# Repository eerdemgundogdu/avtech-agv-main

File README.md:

# AVTECH AGV: Forklift Robot

Software and carrier PCB design for a line-following forklift AGV built by CU AVTECH for the Sanayide Robotik Uygulamalar 2026 competition. The vehicle uses a hoverboard BLDC drivetrain, a Teensy 4.1 for real-time control and a Jetson Orin Nano as its high-level computer.

## Teensy firmware (`teensy_firmware/`)

- Non-blocking, time-sliced main loop: IMU at 100 Hz, motor commands at 20 Hz, telemetry at 10 Hz. No `delay()` calls on the control path.
- Hoverboard driver: speaks the EFeru FOC firmware's USART protocol (speed + steer frames, `0xABCD` start, XOR checksum) and parses feedback frames. Framing, checksum and speed ramping live in `hover_protocol.cpp`, unit-tested on the host.
- IMU: ICM-20948 over SPI with gyro bias calibration and a complementary filter for attitude/yaw.
- Heading hold: PI controller with gyro-rate damping locks the yaw at 50 Hz while driving straight.
- Forklift: DM556 stepper pulsed from an `IntervalTimer` ISR with position tracking, soft limits, homing and a hold-to-move keepalive.
- Navigation FSM: IDLE, MANUAL, LINE_FOLLOW, TURN, PICKUP/DROP, OBSTACLE_STOP and FAULT, plus a line-following PID (QTR-8A or camera offset from Jetson).
- Safety: manual-command timeout with ramp-down, Jetson link watchdog driven by heartbeats, motor outputs zeroed when inactive, and hardware/software E-stop path.
- Command parser: allocation-free JSON line parser with bounded buffers (`cmd_parser.cpp`, host-tested).

All pins, gains and timings are in `config.h`.

## Jetson software (`jetson_software/`)

- `avtech_brain.py`: Flask + Socket.IO control server sending drive input to the Teensy at a fixed 20 Hz with deadman timeout.
- `teensy_link.py`: serial link with PJRC VID auto-detection, port lock, auto-reconnect and 5 Hz heartbeat.
- `camera_node.py`: HSV color-line detection with perspective (bird's-eye) transform and ArUco markers.
- `qr_reader.py`: pick/drop task QR code reader.
- `ekf_localization.py`: Extended Kalman Filter over `[x, y, theta, gyro_bias]` fusing wheel odometry, gyro and QR landmark range/bearing measurements with Mahalanobis outlier gating (`ekf_test.py`).
- `sensor_fusion.py`: wraps the EKF and adds line/obstacle state.
- `mapping_node.py`: 2D occupancy grid built from odometry and ultrasonic sensors.
- `mission_control.py`: task sequencing.

## Carrier board (`hardware/`)

A 2-layer KiCad carrier board for the Teensy 4.1 (Rev A, 105x80 mm). It replaces hand wiring with a 24 V input stage (fuse, reverse-polarity diode, SMBJ30CA TVS), LMR16006X 24 V to 5 V buck, AP2112K-3.3 sensor LDO, BSS138 level shifters, HC-SR04 echo dividers, DM556 open-drain drivers, and a hardware E-stop contactor loop.

The schematic and PCB are generated from `hardware/gen/design.py` and checked with KiCad DRC/ERC. Fabrication outputs (Gerber, drill, BOM, pick-and-place, schematic PDF) are in `hardware/output/`. Design calculations: `hardware/DESIGN.md`; connector pinouts: `hardware/WIRING.md`.

## Testing and Build

```bash
cmake -S firmware_tests -B build/test && cmake --build build/test && ctest --test-dir build/test
cd jetson_software && python3 ekf_test.py
pio run -e teensy41_carrier
```

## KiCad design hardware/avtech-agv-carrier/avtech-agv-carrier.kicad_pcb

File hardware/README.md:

# AVTECH AGV Carrier Board (Rev A)

2-layer (105x80 mm, FR-4, 1.6 mm, 1 oz Cu) carrier board for the Teensy 4.1 forklift AGV.

Subsystems on the board:

- Power input: 1 A fuse, SS16 reverse-polarity diode, SMBJ30CA TVS, 47 uF bulk capacitor.
- 24 V to 5 V buck: LMR16006X (60 V, 0.6 A, 700 kHz), 22 uH inductor.
- 5 V to 3.3 V LDO: AP2112K-3.3 for sensors; Teensy VIN isolated through a B5819W Schottky diode.
- Hardware E-stop: NC button in series with the motor-power contactor coil, plus `MOTOR_EN` low-side switch (`BCP56-16`) and loop sense divider.
- Hoverboard UART: 3-pin connector (15 V pin omitted), 1k series resistors and BAT54S Schottky clamps.
- HC-SR04 x3: 5 V to 3.0 V echo voltage dividers.
- QTR-8A: powered from 3.3 V to keep analog outputs within the Teensy 4.1 ADC range.
- DM556 stepper: common-anode 5 V drive through AO3400A low-side MOSFETs.
- IMU: ICM-20948 over SPI0 with 33 ohm series damping resistors.

## Files

- `DESIGN.md`: design decisions, component calculations, PCB rules and bring-up checklist.
- `WIRING.md`: connector and Teensy 4.1 pin mapping.
- `avtech-agv-carrier/`: KiCad project, schematic and PCB files.
- `output/`: Gerber + drill zip, pick-and-place CSV, BOM, schematic PDF and DRC report.
- `gen/`: generator scripts (`python3 build.py`).

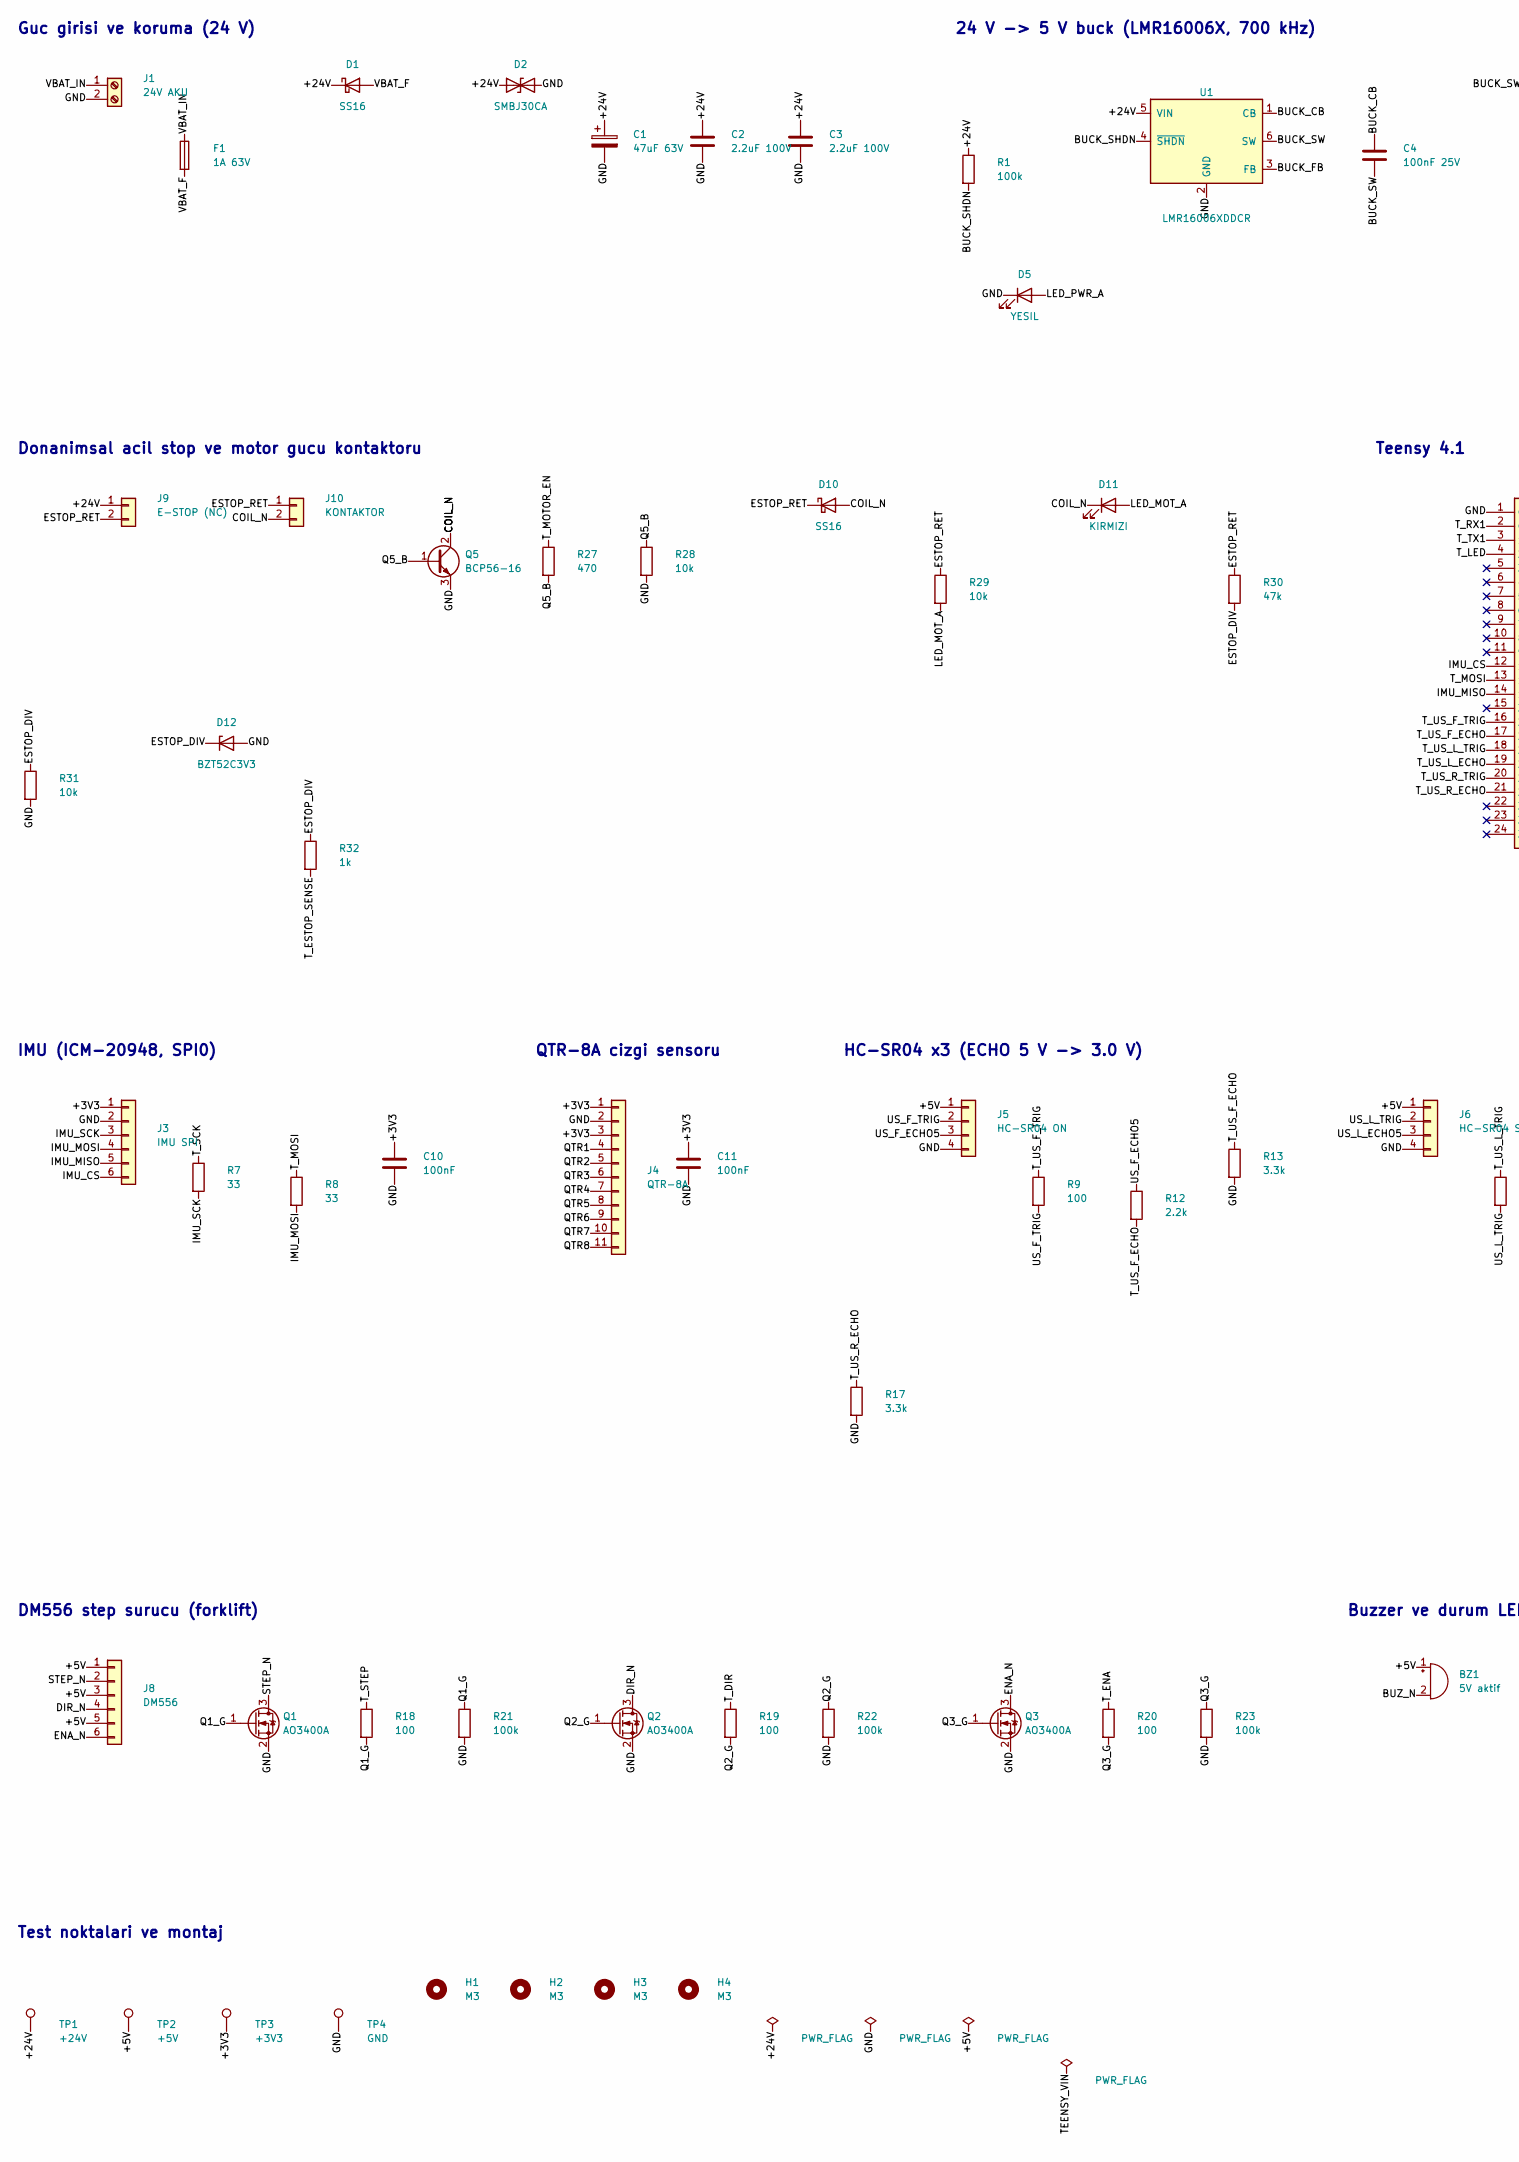
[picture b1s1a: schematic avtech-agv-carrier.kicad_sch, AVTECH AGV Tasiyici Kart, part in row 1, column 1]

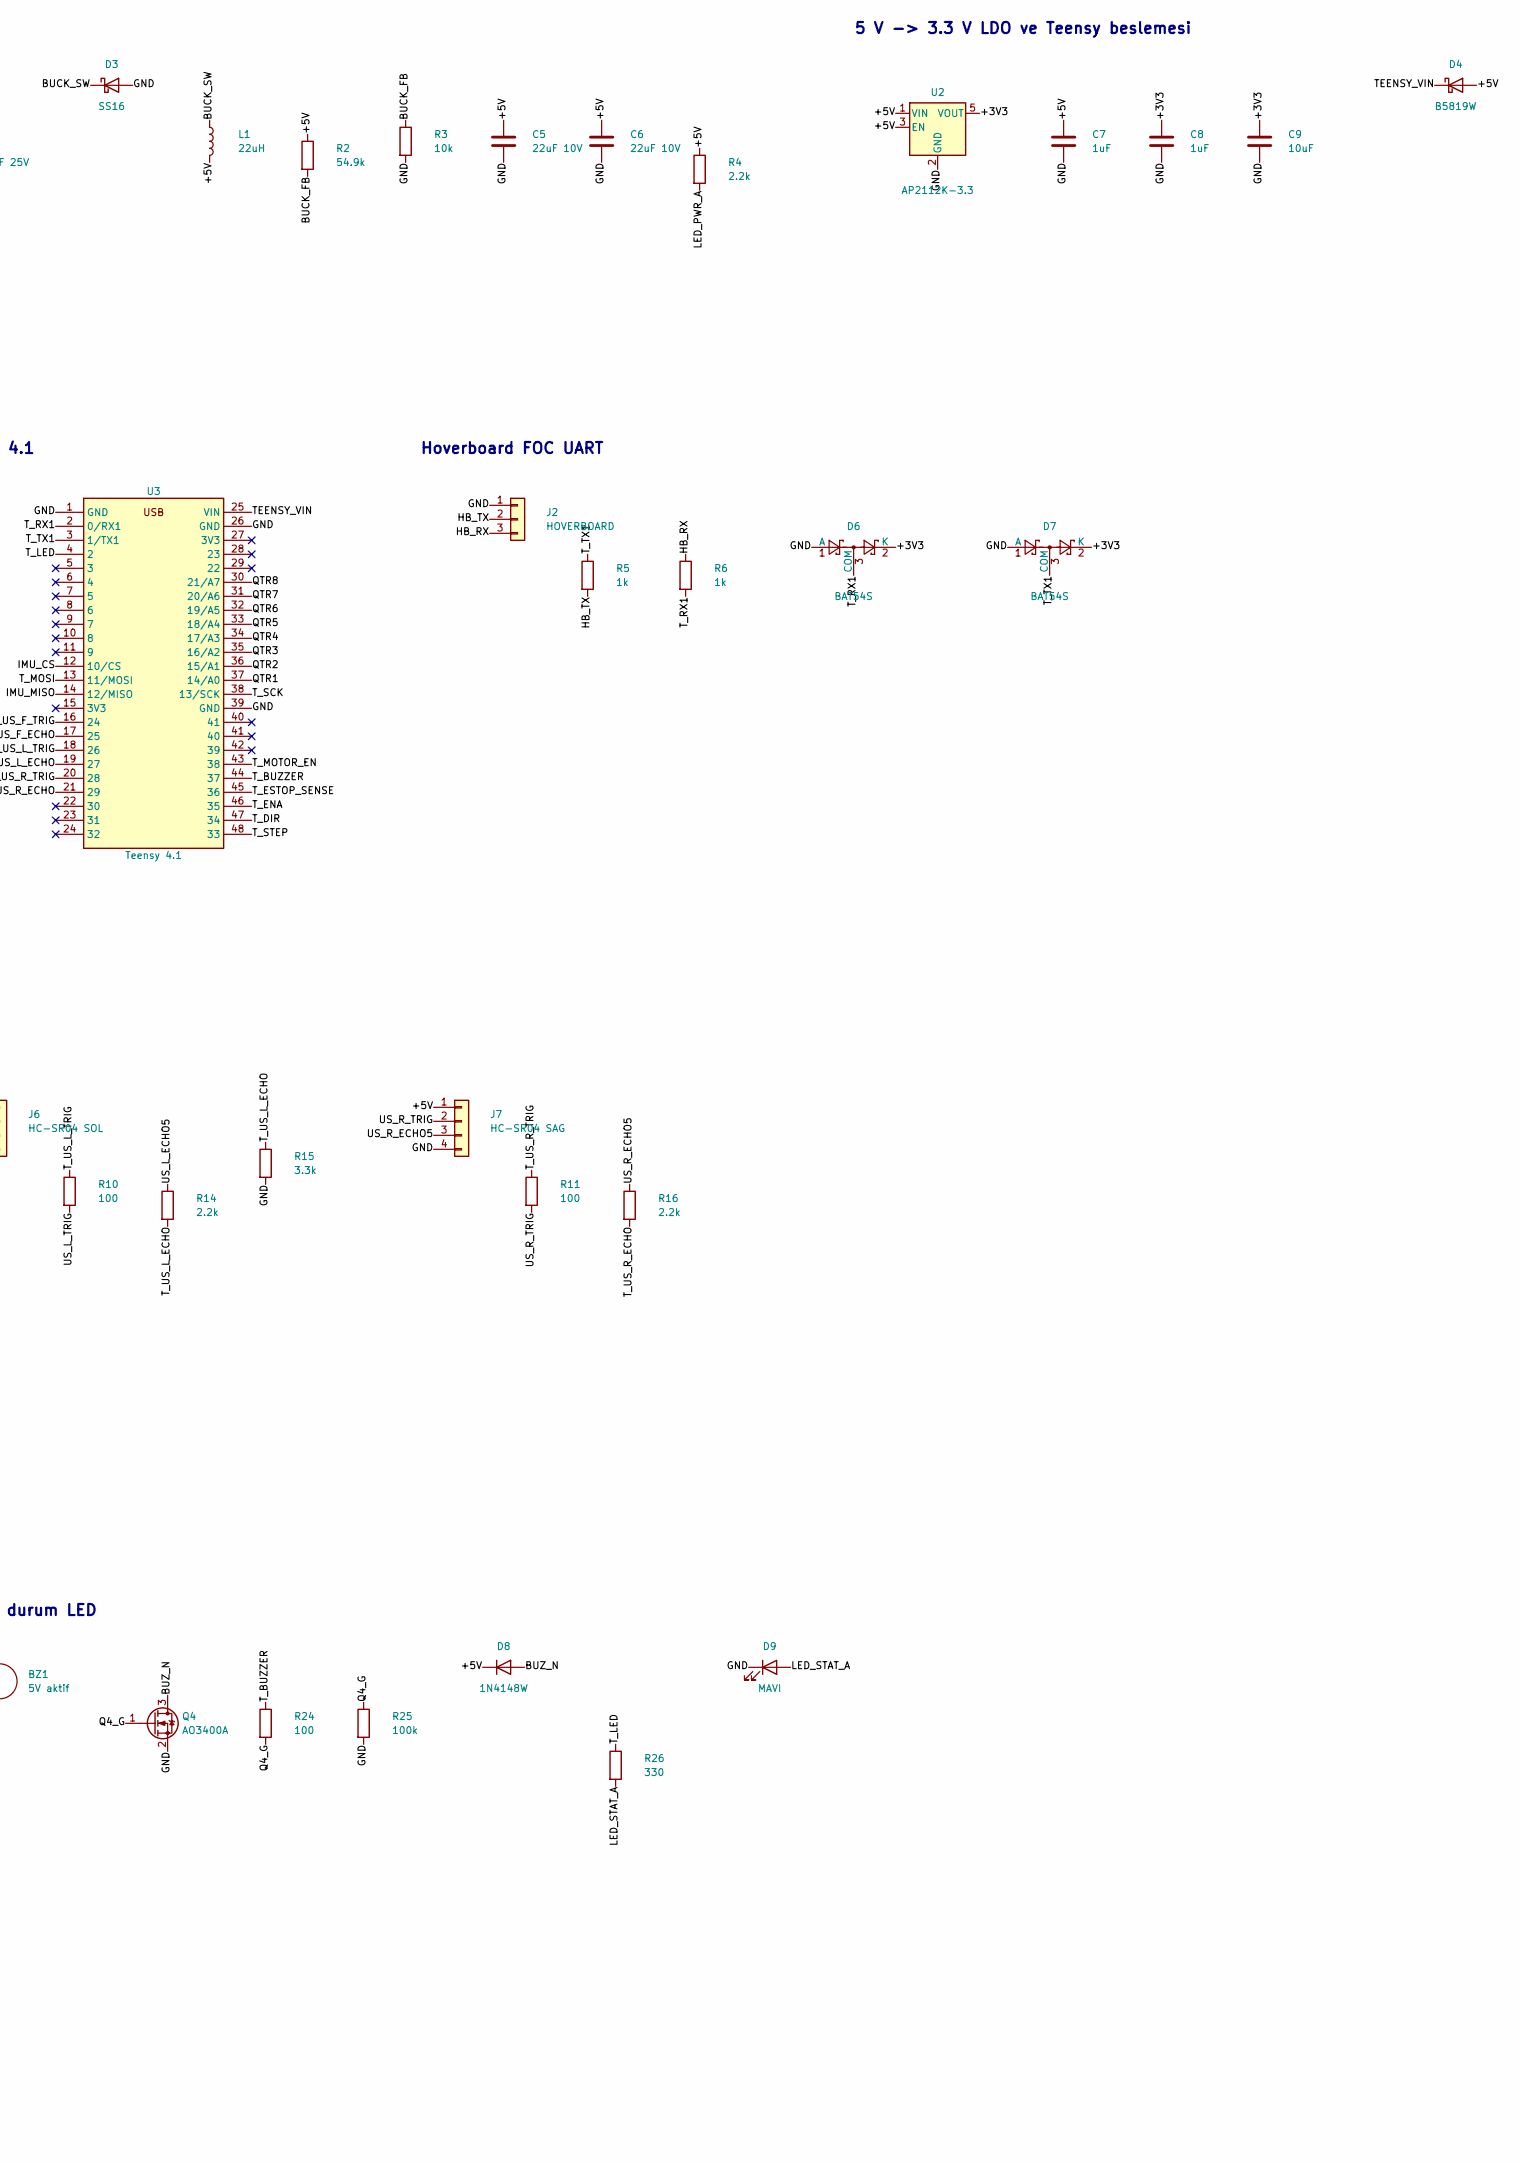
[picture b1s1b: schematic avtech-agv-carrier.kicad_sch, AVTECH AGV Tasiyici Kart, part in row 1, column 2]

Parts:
BZ1: 5V aktif; Buzzer_12x9.5RM7.6; MPN 12 mm 5V aktif buzzer
C1: 47uF 63V; CP_Elec_8x10; MPN Panasonic EEE-FK1J470P
C2, C3: 2.2uF 100V; C_1210_3225Metric; MPN X7R 1210 100V
C4: 100nF 25V; C_0603_1608Metric; MPN X7R 0603 25V
C5, C6: 22uF 10V; C_1206_3216Metric; MPN X7R 1206 10V
C7, C8: 1uF; C_0603_1608Metric; MPN X7R 0603 16V
C9: 10uF; C_0805_2012Metric; MPN X5R 0805 10V
C10, C11: 100nF; C_0603_1608Metric; MPN X7R 0603 16V
D1, D3, D10: SS16; D_SMA; MPN SS16 (60V 1A)
D2: SMBJ30CA; D_SMB; MPN Littelfuse SMBJ30CA
D4: B5819W; D_SOD-123; MPN B5819W (40V 1A)
D5: YESIL; LED_0603_1608Metric; MPN 0603 yesil LED
D6, D7: BAT54S; SOT-23; MPN BAT54S
D8: 1N4148W; D_SOD-323; MPN 1N4148WS
D9: MAVI; LED_0603_1608Metric; MPN 0603 mavi LED
D11: KIRMIZI; LED_0603_1608Metric; MPN 0603 kirmizi LED
D12: BZT52C3V3; D_SOD-123; MPN BZT52C3V3
F1: 1A 63V; Fuse_1206_3216Metric; MPN Littelfuse 0466001.NRHF
H1, H2, H3, H4: M3; MountingHole_3.2mm_M3
J1: 24V AKU; TerminalBlock_Phoenix_MKDS-1,5-2-5.08_1x02_P5.08mm_Horizont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; MPN Phoenix 1715721
J2: HOVERBOARD; JST_XH_B3B-XH-A_1x03_P2.50mm_Vertical; MPN JST B3B-XH-A
J3: IMU SPI; JST_XH_B6B-XH-A_1x06_P2.50mm_Vertical; MPN JST B6B-XH-A
J4: QTR-8A; JST_XH_B11B-XH-A_1x11_P2.50mm_Vertical; MPN JST B11B-XH-A
J5: HC-SR04 ON; JST_XH_B4B-XH-A_1x04_P2.50mm_Vertical; MPN JST B4B-XH-A
J6: HC-SR04 SOL; JST_XH_B4B-XH-A_1x04_P2.50mm_Vertical; MPN JST B4B-XH-A
J7: HC-SR04 SAG; JST_XH_B4B-XH-A_1x04_P2.50mm_Vertical; MPN JST B4B-XH-A
J8: DM556; JST_XH_B6B-XH-A_1x06_P2.50mm_Vertical; MPN JST B6B-XH-A
J9: E-STOP (NC); JST_XH_B2B-XH-A_1x02_P2.50mm_Vertical; MPN JST B2B-XH-A
J10: KONTAKTOR; JST_XH_B2B-XH-A_1x02_P2.50mm_Vertical; MPN JST B2B-XH-A
L1: 22uH; L_Bourns_SRN6045TA; MPN Bourns SRN6045TA-220M
Q1, Q2, Q3, Q4: AO3400A; SOT-23; MPN AOS AO3400A
Q5: BCP56-16; SOT-223-3_TabPin2; MPN Nexperia BCP56-16
R1, R21, R22, R23, R25: 100k; R_0603_1608Metric; MPN 0603 100k 1%
R2: 54.9k; R_0603_1608Metric; MPN 0603 54.9k 1%
R3, R28, R29, R31: 10k; R_0603_1608Metric; MPN 0603 10k 1%
R4, R12, R14, R16: 2.2k; R_0603_1608Metric; MPN 0603 2.2k 1%
R5, R6, R32: 1k; R_0603_1608Metric; MPN 0603 1k 1%
R7, R8: 33; R_0603_1608Metric; MPN 0603 33 1%
R9, R10, R11, R18, R19, R20, R24: 100; R_0603_1608Metric; MPN 0603 100 1%
R13, R15, R17: 3.3k; R_0603_1608Metric; MPN 0603 3.3k 1%
R26: 330; R_0603_1608Metric; MPN 0603 330 1%
R27: 470; R_0603_1608Metric; MPN 0603 470 1%
R30: 47k; R_0603_1608Metric; MPN 0603 47k 1%
TP1: +24V; TestPoint_Pad_D1.5mm
TP2: +5V; TestPoint_Pad_D1.5mm
TP3: +3V3; TestPoint_Pad_D1.5mm
TP4: GND; TestPoint_Pad_D1.5mm
U1: LMR16006XDDCR; SOT-23-6; MPN TI LMR16006XDDCR
U2: AP2112K-3.3; SOT-23-5; MPN Diodes AP2112K-3.3TRG1
U3: Teensy 4.1; Teensy4.1_Socket; MPN PJRC Teensy 4.1 + 2x 1x24 disi header

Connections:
+3V3: C8.1, C9.1, C10.1, C11.1, D6.2 (K), D7.2 (K), J3.1, J4.1, J4.3, TP3.1, U2.5 (VOUT)
+5V: BZ1.1 (+), C5.1, C6.1, C7.1, D4.2 (A), D8.1 (K), J5.1, J6.1, J7.1, J8.1, J8.3, J8.5, L1.2, R2.1, R4.1, TP2.1, U2.1 (VIN), U2.3 (EN)
+24V: C1.1, C2.1, C3.1, D1.1 (K), D2.1 (A1), J9.1, R1.1, TP1.1, U1.5 (VIN)
BUCK_CB: C4.1, U1.1 (CB)
BUCK_FB: R2.2, R3.1, U1.3 (FB)
BUCK_SHDN: R1.2, U1.4 (~SHDN)
BUCK_SW: C4.2, D3.1 (K), L1.1, U1.6 (SW)
BUZ_N: BZ1.2 (-), D8.2 (A), Q4.3 (D)
COIL_N: D10.2 (A), D11.1 (K), J10.2, Q5.2 (C), Q5.4 (C)
DIR_N: J8.4, Q2.3 (D)
ENA_N: J8.6, Q3.3 (D)
ESTOP_DIV: D12.1 (K), R30.2, R31.1, R32.1
ESTOP_RET: D10.1 (K), J9.2, J10.1, R29.1, R30.1
GND: C1.2, C2.2, C3.2, C5.2, C6.2, C7.2, C8.2, C9.2, C10.2, C11.2, D2.2 (A2), D3.2 (A), D5.1 (K), D6.1 (A), D7.1 (A), D9.1 (K), D12.2 (A), J1.2, J2.1, J3.2, J4.2, J5.4, J6.4, J7.4, Q1.2 (S), Q2.2 (S), Q3.2 (S), Q4.2 (S), Q5.3 (E), R3.2, R13.2, R15.2, R17.2, R21.2, R22.2, R23.2, R25.2, R28.2, R31.2, TP4.1, U1.2 (GND), U2.2 (GND), U3.1 (GND), U3.26 (GND), U3.39 (GND)
HB_RX: J2.3, R6.1
HB_TX: J2.2, R5.2
IMU_CS: J3.6, U3.12 (10/CS)
IMU_MISO: J3.5, U3.14 (12/MISO)
IMU_MOSI: J3.4, R8.2
IMU_SCK: J3.3, R7.2
LED_MOT_A: D11.2 (A), R29.2
LED_PWR_A: D5.2 (A), R4.2
LED_STAT_A: D9.2 (A), R26.2
Q1_G: Q1.1 (G), R18.2, R21.1
Q2_G: Q2.1 (G), R19.2, R22.1
Q3_G: Q3.1 (G), R20.2, R23.1
Q4_G: Q4.1 (G), R24.2, R25.1
Q5_B: Q5.1 (B), R27.2, R28.1
QTR1: J4.4, U3.37 (14/A0)
QTR2: J4.5, U3.36 (15/A1)
QTR3: J4.6, U3.35 (16/A2)
QTR4: J4.7, U3.34 (17/A3)
QTR5: J4.8, U3.33 (18/A4)
QTR6: J4.9, U3.32 (19/A5)
QTR7: J4.10, U3.31 (20/A6)
QTR8: J4.11, U3.30 (21/A7)
STEP_N: J8.2, Q1.3 (D)
TEENSY_VIN: D4.1 (K), U3.25 (VIN)
T_BUZZER: R24.1, U3.44 (37)
T_DIR: R19.1, U3.47 (34)
T_ENA: R20.1, U3.46 (35)
T_ESTOP_SENSE: R32.2, U3.45 (36)
T_LED: R26.1, U3.4 (2)
T_MOSI: R8.1, U3.13 (11/MOSI)
T_MOTOR_EN: R27.1, U3.43 (38)
T_RX1: D6.3 (COM), R6.2, U3.2 (0/RX1)
T_SCK: R7.1, U3.38 (13/SCK)
T_STEP: R18.1, U3.48 (33)
T_TX1: D7.3 (COM), R5.1, U3.3 (1/TX1)
T_US_F_ECHO: R12.2, R13.1, U3.17 (25)
T_US_F_TRIG: R9.1, U3.16 (24)
T_US_L_ECHO: R14.2, R15.1, U3.19 (27)
T_US_L_TRIG: R10.1, U3.18 (26)
T_US_R_ECHO: R16.2, R17.1, U3.21 (29)
T_US_R_TRIG: R11.1, U3.20 (28)
US_F_ECHO5: J5.3, R12.1
US_F_TRIG: J5.2, R9.2
US_L_ECHO5: J6.3, R14.1
US_L_TRIG: J6.2, R10.2
US_R_ECHO5: J7.3, R16.1
US_R_TRIG: J7.2, R11.2
VBAT_F: D1.2 (A), F1.2
VBAT_IN: F1.1, J1.1

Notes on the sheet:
Guc girisi ve koruma (24 V)
24 V -> 5 V buck (LMR16006X, 700 kHz)
5 V -> 3.3 V LDO ve Teensy beslemesi
Donanimsal acil stop ve motor gucu kontaktoru
Teensy 4.1
Hoverboard FOC UART
IMU (ICM-20948, SPI0)
QTR-8A cizgi sensoru
HC-SR04 x3 (ECHO 5 V -> 3.0 V)
DM556 step surucu (forklift)
Buzzer ve durum LED
Test noktalari ve montaj

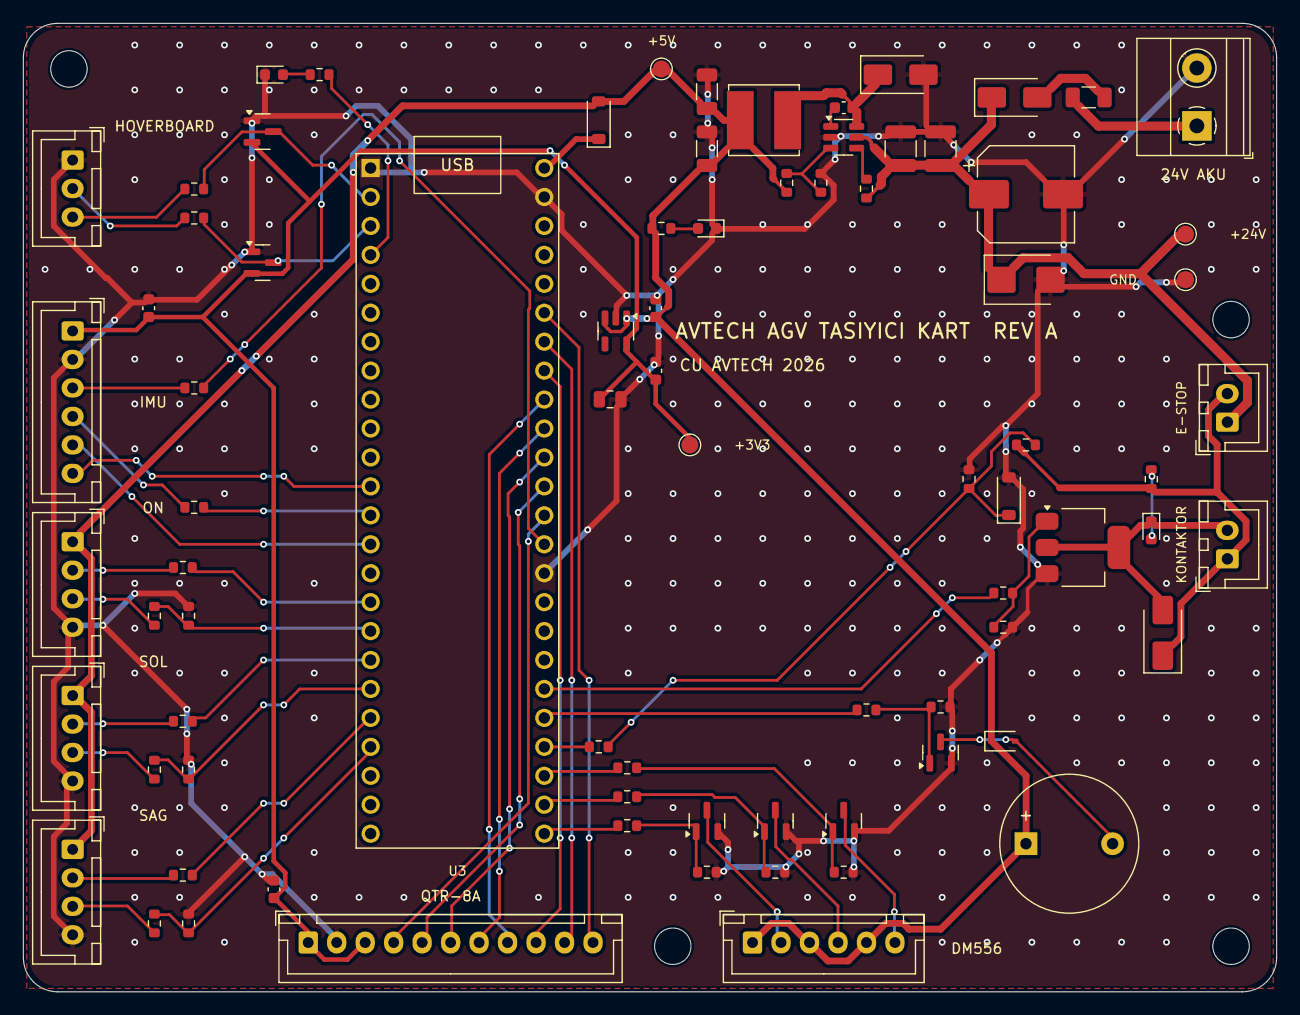
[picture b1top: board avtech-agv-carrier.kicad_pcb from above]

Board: 2 copper layers, 110.0 x 85.0 mm, 84 parts (0 on the bottom side), 63 nets.

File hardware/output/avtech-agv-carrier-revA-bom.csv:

Adet,Referanslar,Deger,Footprint,Parca,Not
1,BZ1,5V aktif,Buzzer_12x9.5RM7.6,12 mm 5V aktif buzzer,
1,C1,47uF 63V,CP_Elec_8x10,Panasonic EEE-FK1J470P,Toplu giris kondansatoru
2,C2 C3,2.2uF 100V,C_1210_3225Metric,X7R 1210 100V,
1,C4,100nF 25V,C_0603_1608Metric,X7R 0603 25V,
2,C5 C6,22uF 10V,C_1206_3216Metric,X7R 1206 10V,
2,C7 C8,1uF,C_0603_1608Metric,X7R 0603 16V,
1,C9,10uF,C_0805_2012Metric,X5R 0805 10V,
2,C10 C11,100nF,C_0603_1608Metric,X7R 0603 16V,
3,D1 D3 D10,SS16,D_SMA,SS16 (60V 1A),Bobin serbest gecis diyodu; Buck serbest gecis (catch) diyodu; Ters kutup korumasi
1,D2,SMBJ30CA,D_SMB,Littelfuse SMBJ30CA,Vrwm 30V; motor kaynakli sicramalar
1,D4,B5819W,D_SOD-123,B5819W (40V 1A),USB 5V ile kart 5V birbirini beslemesin
1,D5,YESIL,LED_0603_1608Metric,0603 yesil LED,+5V var
2,D6 D7,BAT54S,SOT-23,BAT54S,RX kiskaci; TX kiskaci
1,D8,1N4148W,D_SOD-323,1N4148WS,Buzzer serbest gecis
1,D9,MAVI,LED_0603_1608Metric,0603 mavi LED,Durum (pin 2)
1,D11,KIRMIZI,LED_0603_1608Metric,0603 kirmizi LED,Motor gucu acik
1,D12,BZT52C3V3,D_SOD-123,BZT52C3V3,3.3 V kiskac
1,F1,1A 63V,Fuse_1206_3216Metric,Littelfuse 0466001.NRHF,Lojik + kontaktor bobini
1,J1,24V AKU,"TerminalBlock_Phoenix_MKDS-1,5-2-5.08_1x02_P5.08mm_Horizontal",Phoenix 1715721,Aku girisi (sigortali hattan)
1,J2,HOVERBOARD,JST_XH_B3B-XH-A_1x03_P2.50mm_Vertical,JST B3B-XH-A,15V pini bilerek yok
1,J3,IMU SPI,JST_XH_B6B-XH-A_1x06_P2.50mm_Vertical,JST B6B-XH-A,
1,J4,QTR-8A,JST_XH_B11B-XH-A_1x11_P2.50mm_Vertical,JST B11B-XH-A,Pin 3 = LEDON (hep acik)
1,J5,HC-SR04 ON,JST_XH_B4B-XH-A_1x04_P2.50mm_Vertical,JST B4B-XH-A,
1,J6,HC-SR04 SOL,JST_XH_B4B-XH-A_1x04_P2.50mm_Vertical,JST B4B-XH-A,
1,J7,HC-SR04 SAG,JST_XH_B4B-XH-A_1x04_P2.50mm_Vertical,JST B4B-XH-A,
1,J8,DM556,JST_XH_B6B-XH-A_1x06_P2.50mm_Vertical,JST B6B-XH-A,PUL+ PUL- DIR+ DIR- ENA+ ENA-
1,J9,E-STOP (NC),JST_XH_B2B-XH-A_1x02_P2.50mm_Vertical,JST B2B-XH-A,Normalde kapali buton
1,J10,KONTAKTOR,JST_XH_B2B-XH-A_1x02_P2.50mm_Vertical,JST B2B-XH-A,"24V bobin, <= 0.4 A"
1,L1,22uH,L_Bourns_SRN6045TA,Bourns SRN6045TA-220M,Isat >= 1 A gerekli
4,Q1 Q2 Q3 Q4,AO3400A,SOT-23,AOS AO3400A,
1,Q5,BCP56-16,SOT-223-3_TabPin2,Nexperia BCP56-16,80V 1A; hFE 100-250
5,R1 R21 R22 R23 R25,100k,R_0603_1608Metric,0603 100k 1%,
1,R2,54.9k,R_0603_1608Metric,0603 54.9k 1%,
4,R3 R28 R29 R31,10k,R_0603_1608Metric,0603 10k 1%,
4,R4 R12 R14 R16,2.2k,R_0603_1608Metric,0603 2.2k 1%,
3,R5 R6 R32,1k,R_0603_1608Metric,0603 1k 1%,
2,R7 R8,33,R_0603_1608Metric,0603 33 1%,
7,R9 R10 R11 R18 R19 R20 R24,100,R_0603_1608Metric,0603 100 1%,
3,R13 R15 R17,3.3k,R_0603_1608Metric,0603 3.3k 1%,
1,R26,330,R_0603_1608Metric,0603 330 1%,
1,R27,470,R_0603_1608Metric,0603 470 1%,
1,R30,47k,R_0603_1608Metric,0603 47k 1%,
1,U1,LMR16006XDDCR,SOT-23-6,TI LMR16006XDDCR,X versiyonu (700 kHz); sembol Y ile pin uyumlu
1,U2,AP2112K-3.3,SOT-23-5,Diodes AP2112K-3.3TRG1,600 mA; QTR-8A + IMU
1,U3,Teensy 4.1,Teensy4.1_Socket,PJRC Teensy 4.1 + 2x 1x24 disi header,Tum 3.3V pinleri bos; VIN D4 uzerinden
